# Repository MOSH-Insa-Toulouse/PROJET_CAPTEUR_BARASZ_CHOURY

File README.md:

# PROJET_CAPTEUR_BARASZ_CHOURY
 
## SOMMAIRE 
* 1 [Introduction](#introduction)
* 2 [Installation de la chaine de mesure](#paragraph2)
* 3 [Modélisation de la carte PCB sur KiCad](#paragraph3)
* 4 [Fabrication du shield et soudure des composants](#paragraph4)
* 5 [Arduino UNO](#paragraph5) 
    *  5.1 [Description du code](#subparagraph5.1) 
    *  5.2 [Bibliothèques Arduino](#subparagraph5.2)
* 6 [Application APK](#paragraph6)
* 7 [Mise en oeuvre du banc de test](#paragraph7)
    *  7.1 [Protocole](#paragraph7.1)
    *  7.2 [Résultats obtenus](#paragraph7.2)
* 8 [Améliorations à apporter](#paragraph8)

--------- 
## Introduction 
2020-2021 : Ce projet a été réalisé dans le cadre de l'unité de formation _"Du capteur au banc de test"_ de 4ième année Génie Physique à l'INSA Toulouse.
L’objectif est la conception d’un capteur de déformation (jauge de déformation) à base de graphite, peu coûteux, flexible, léger, et avant tout écoresponsable. 

Le coloriage au crayon laisse une fine couche de graphite sur le papier. Cette couche de graphite possède un réseau percolé caractéristique. Toute déformation de ce réseau induit une variation de la distance entre les nanoparticules de graphite. Cette dernière est à l’origine de la modification de la conductivité électrique/résistance de la couche de graphite. 

Souhaitant acquérir et exploiter le signal associé à la résistance du capteur, nous avons réalisé un shield PCB, à l’aide du logiciel KiCad contenant un amplificateur transimpédance, des interfaces pour un module bluetooth, un écran OLED, et un encordeur rotatoir. Ce shiled PCB est ensuite inséré sur un microcontrôleur Arduino Uno, programmé à l’aide du logiciel Arduino IDE en C++. Les mesures de résistances sont également transmises par Bluetooth et répertoriées sur notre application android APK créée sur MIT App Inventor. 

La chaîne de mesure fin prête, nous avons mis au point un banc de test permettant l'étude de la variation relative de la résistance de différents type de capteurs lors de déformation en compression et tension. 

--------------------

## Installation de la chaine de mesure 

    - Imprimer le PCB, préalablement designé sur KiCad, grâce à l'empreinte Gerber. 
  
    - Vérifier l'état des pistes. 
  
    - Souder les composants et brancher l'OLED, l'encodeur rotatoir et le module Bluetooth. 
  
    - Connecter le PCB sur la carte Arduino Uno.
  
    - Connecter le microcontrolleur Arduino Uno au PC grâce au cable USB. 
  
    - Ouvrir le programme Arduino (voir dossier Arduino).   
      Sélectionner au préalable le bon port de communication Arduino puis compiler et téléverser le programme. 
  
Les valeurs de résistance/tension sont directement affichées sur l'écran OLED. Grâce à l'encodeur rotatoir, vous pouvez décider d'afficher la grandeur souhaitée. Ces dernières sont aussi disponibles sur le moniteur Arduino.
Vous pouvez aussi télécharger notre application APK pour obtenir directement les valeurs sur votre smartphone grâce à votre connexion Bluetooth. 

-------------------

## Modélisation de la carte PCB sur KiCad 

Réalisation de la carte PCB sur KiCad  
   
    - Creation des symboles de l'OLED, le module bluetooth, l'encodeur rotatoir et le capteur graphite.
      Tous les symboles sont répertoriés dans le dossier KiCad. 

    - Schéma electrique du circuit sur eeschema. Sur ce shéma, vous trouverez un amplificateur transimpédance,
      l'écran OLED, le module Bluetooth et l'encodeur rotatoire. En haut à droite les pins de la carte Arduino
      sont représentées.  

    - Routage des pistes sur pcbnew.

Visualisation 2D du shield 

Visualisation 3D du shield

-------------------

## Fabrication du shield et soudure des composants 

Avec l'aide de Mme Cathy Crouzet, nous avons fabriqué la carte PCB modélisée au préalable sur le logiciel KiCad. Notre carte PCB est constituée d'une plaque isolante d'epoxy recouverte d'une très fine feuille de cuivre. Une couche de résine photosensible est déposée sur ce support epoxy cuivré.

Tout d'abord, le tracé de notre modélisation PCB est imprimé sur un support transparant aux ultraviolets de type papier calque : on obtient le masque (ou typon). Celui ci est placé sur la plaquette epoxy, dans l'insoleuse à tube UV, en prenant soin de poser le côté encré au contact du cuivre. Lors de l'insolation de la plaque (réalisée en 1'30"- 2'30"), les parties du typon correspondant aux pistes du circuit empêchent les UV d'atteindre la surface sensible.   
La plaque est ensuite plongée quelques secondes dans un liquide appelé révélateur. Celui ci dissout la résine exposée aux UV lors de l'insolation. A la fin de cette étape, la résine est seulement conservée dans les zones destinées aux pistes de notre circuit.

Après une étape de rinçage à l'eau courante, la plaquette doit par la suite être gravée. Pour cela, nous la plongeons dans un bain de perchlorure de fer pendant 10 minutes environ. Les parties de cuivre non protégées par la résine photosensible sont ici dissoues. Enfin, la dernière étape du processus consiste à retirer l'excès de résine en utilisant de l'acétone. 

La carte PCB ainsi obtenue est fin prête pour les étapes de perçage et de mise en place des composants. 

  * Perçage des trous de la plaque obtenugrâce à une perçeuse électrique 
Nous perçons des trous de diamètre égale à :
      * 0.8mm pour l'AOP, les résistances et les capacités.
      * 1mm pour les connecteurs de l'Arduino, le module Bluetooth, l'écran OLED, l'encodeur rotatoire et les pinces du capteur.
 
  * Soudure des composants
 
Les composants sont soudés sur la carte PCB à l'aide d'un fer à souder. 
 
----------------------

## Arduino UNO 

### Description du code 

Le code Arduino permet de lire les valeurs de tension du capteur de graphite et calcule la valeur de résistance correspondante. Il assure l'affichage des valeurs de tension et de résistance sur un écran OLED. De plus, le code permet la gestion d'un menu via l'encodeur rotatoire: l'utilisateur peut décider d'afficher la valeur de la résistance ou bien celle de la tension. 

Le code permet aussi de communiquer par Bluetooth avec le télephone portable grâce. Il envoie la mesure de la tension du capteur de graphite par Bluetooth. 

### Bibliothèques Arduino 

Afin d'utiliser le code Arduino, il vous faudra au préalable télécharger des bibliothèques Arduino.

À installer depuis l'IDE ou GitHub :

- Adafruit GFX Library : https://github.com/adafruit/Adafruit-GFX-Library
- Adafruit SSD1306 : https://github.com/adafruit/Adafruit_SSD1306
- Adafruit BusIO : https://github.com/adafruit/Adafruit_BusIO  

Vous pouvez aussi télécharger ces bibliothèques direcetement sur l'application Arduino

1) Dans l’IDE Arduino cliquez sur "croquis", allez sur "inclure un bibliothèque" puis cliquez sur  "Gerer les bibliothèques".  

2) Une fenêtre apparait. Tappez le nom de la bibliothèques que vous voulez ajouter dans la barre de recherche et cliquez sur  "Installer".Fermez la fenêtre.  

3) Dans l’IDE Arduino cliquez sur "croquis", allez sur "inclure un bibliothèque". A la fin dans les "bibliothèques contribuées" doit se trouver votre biblothèques téléchargée.  

4) Afin de savoir comment fonctionne la bibliothèque installée, vous pourrez vous servir de la page d’aide qui accompagne généralement la bibliothèque ou alors vous aider des exemples fournis avec celle-ci disponible ici :  

------------------------------

## Application APK 

L'application APK est une applictaion pour smartphone utilisant le système d'exploitation Android. 
Vous pouvez télecharger l'application grâce au fichier .apk qui vous est fourni dans notre dossier APK Bluetooth.  
Si vous souhaitez modifier l'application, vous pouvez utiliser le fichier .aia sur l'application en ligne _MIT APP INVENTOR_.  

Notre application est à mettre en relation avec le code Arduino développé pour mesurer la tension de la couche de graphite. L'application permet de :
  * se connecter à un module Bluetooth.
  * une fois connecté, relever la  valeur de la tension de la couche de graphite envoyée par Bluetooth.
  * calculer la résistance correspondante.
  * afficher ces deux valeurs de tension et de résistance
  * tracer un graphe décrivant l'évolution de la tension au cours du temps.  

----------------------------

## Mise en oeuvre du banc de test  

### Protocole 

Le protocole du banc de test est détaillé dans le fichier "Protocole du banc de test". Veuillez trouver ci joint le lien de ce fichier :https://github.com/MOSH-Insa-Toulouse/PROJET_CAPTEUR_BARASZ_CHOURY/blob/c4a42f93ef4b2496bb2e2b371ca4b9b335598a01/Banc%20de%20test/Protocole%20de%20notre%20banc%20de%20test.pdf

### Résultats obtenus 

Résultats obtenus sont détaillés au lien suivant : https://github.com/MOSH-Insa-Toulouse/PROJET_CAPTEUR_BARASZ_CHOURY/blob/7fd93865a4fc5e2c620f3dd2ebc7bdd68492d652/Banc%20de%20test/R%C3%A9sultats%20Banc%20de%20Test.xlsx 

Les analyses de nos résultats : https://github.com/MOSH-Insa-Toulouse/PROJET_CAPTEUR_BARASZ_CHOURY/blob/7fd93865a4fc5e2c620f3dd2ebc7bdd68492d652/Banc%20de%20test/Analyse%20de%20nos%20r%C3%A9sultats%20banc%20de%20test.pdf 

----------------------------

## Améliorations à apporter  
 
Notre banc de test présente certaines limites. On peut critiquer notamment : 
   - le dépôt de graphite sur le papier : on ne peut maitriser la quantité de graphite déposée sur le papier, la précision du coloriage.
   - la non répétabilité de la mesure. En effet, entre chaque série de mesures, les déformations appliquées peuvent varier: le banc de test ne permet pas d’appliquer une       déformation identique. On pourrait envisager un banc de test fonctionnant avec un servomoteur par exemple. Ce système permet de générer des contraintes avec des consignes d’angles bien présice et d'obtenir, de ce fait, une meilleure reproductibilité. 
   - la déformation irréversible du capteur entre chaque série de mesures. 

Notre carte shield peut être également améliorée. En effet, afin de pouvoir lire une plus grande plage de résistance tout en ayant des mesures stables, il faudrait pouvoir changer le gain du circuit transimpédance c'est à dire modifier la résistance R2 (voir schéma KiCad ). Cependant nous l'avons soudée sur le circuit PCB. Il aurait donc fallu : 
    
   - ne pas souder cette résistance pour pouvoir mettre des résistances différentes
   - souder une résistance variable (potentiomètre).   

Un code Arduino plus complet pourrait également être développé. Si nous travaillons avec une résistance R2 variable, le code doit prendre en compte la modification de la valeur de R2. Le code Arduino pourrait gérer un encodeur rotatoire permttant de modifier la valeur de R2 dans le code.

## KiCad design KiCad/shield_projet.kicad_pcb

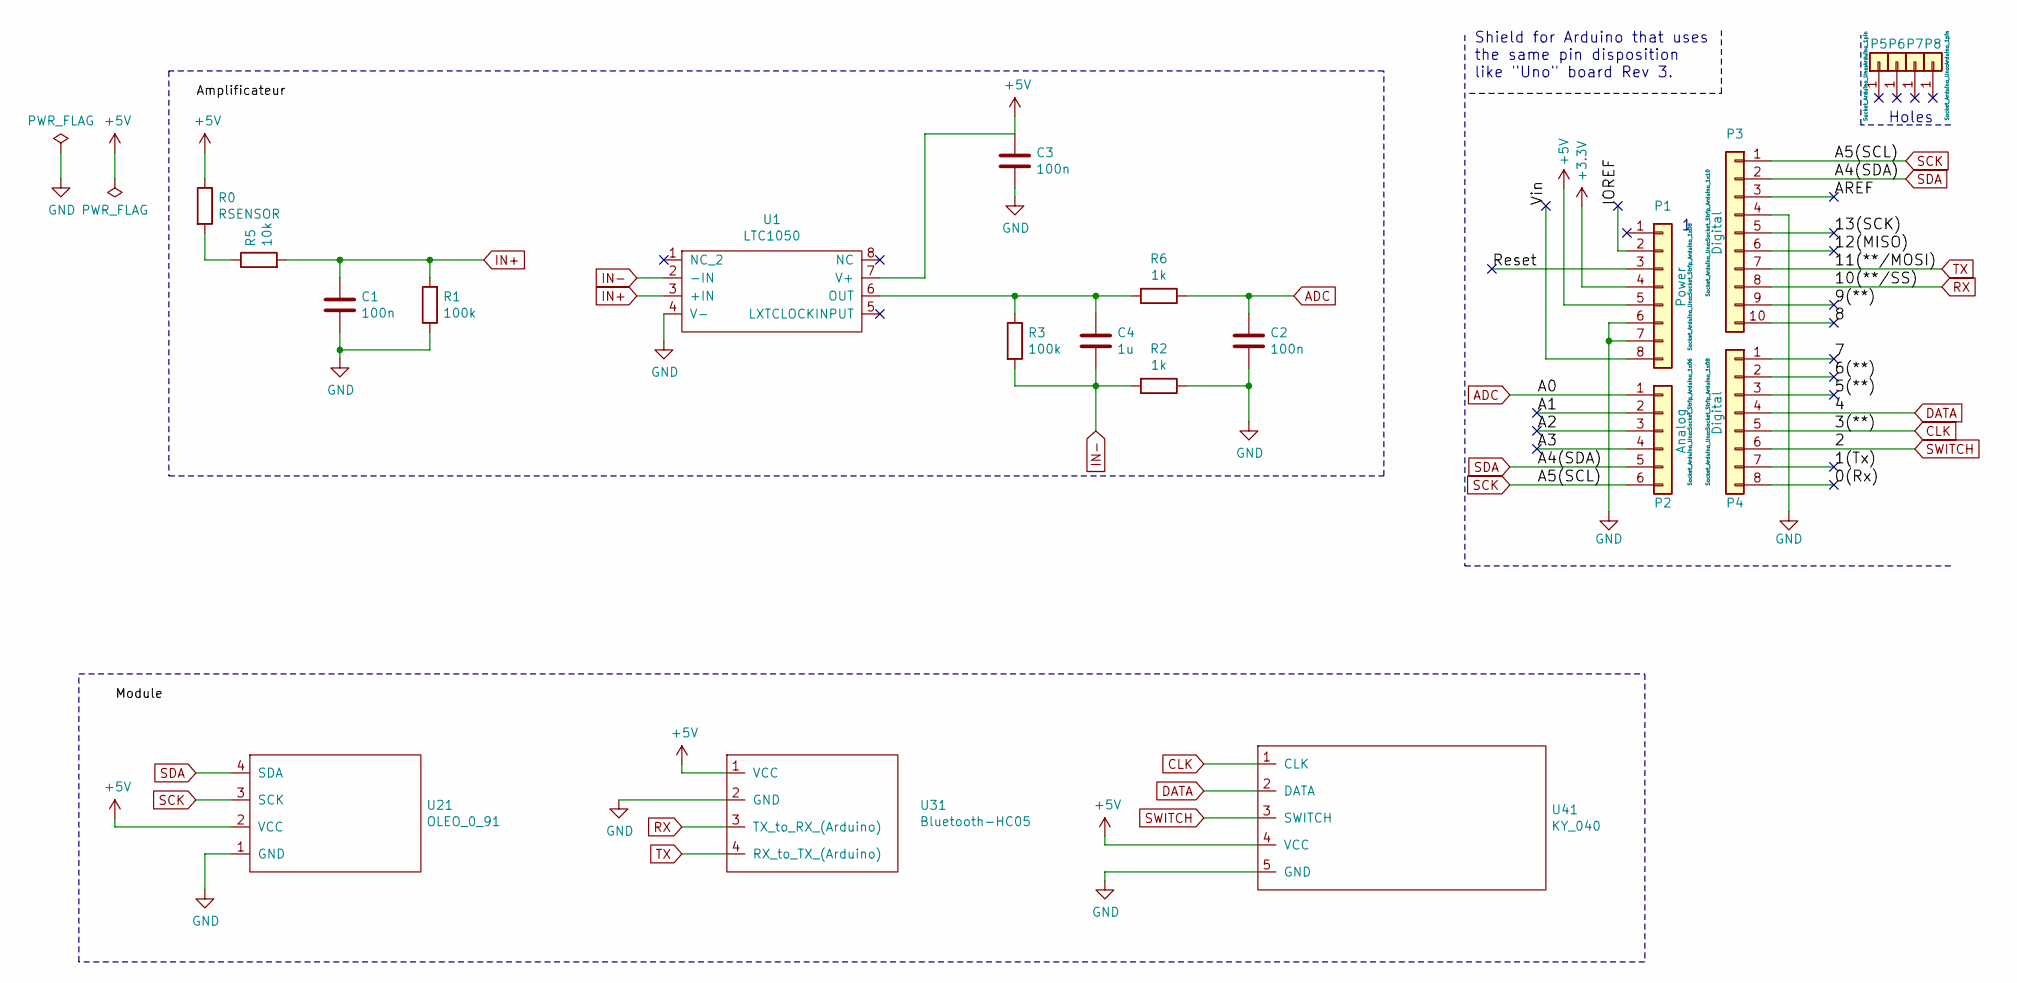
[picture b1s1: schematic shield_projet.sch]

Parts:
C1, C2, C3: 100n; C_Axial_L5.1mm_D3.1mm_P7.50mm_Horizontal
C4: 1u; C_Axial_L5.1mm_D3.1mm_P7.50mm_Horizontal
P1: Power; Socket_Strip_Arduino_1x08
P2: Analog; Socket_Strip_Arduino_1x06
P3: Digital; Socket_Strip_Arduino_1x10
P4: Digital; Socket_Strip_Arduino_1x08
P5, P6, P7, P8: CONN_01X01; Arduino_1pin
R0: RSENSOR; R_Axial_DIN0207_L6.3mm_D2.5mm_P10.16mm_Horizontal
R1, R3: 100k; R_Axial_DIN0207_L6.3mm_D2.5mm_P10.16mm_Horizontal
R2, R6: 1k; R_Axial_DIN0207_L6.3mm_D2.5mm_P10.16mm_Horizontal
R5: 10k; R_Axial_DIN0207_L6.3mm_D2.5mm_P10.16mm_Horizontal
U1: LTC1050; DIP-8_296
U21: OLEO_0_91; SIP-4
U31: Bluetooth-HC05; SIP-4_bt
U41: KY_040; SIP-5

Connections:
+3V3: P1.4
+5V: C3.1, P1.5, R0.1, U1.7 (V+), U21.2 (VCC), U31.1 (VCC), U41.4 (VCC)
/0(Rx): P4.8
/1(Tx): P4.7
/5(**): P4.3
/6(**): P4.2
/7: P4.1
/8: P3.10
/9(**): P3.9
/12(MISO): P3.6
/13(SCK): P3.5
/A1: P2.2
/A2: P2.3
/A3: P2.4
/AREF: P3.3
/IOREF: P1.2
/Reset: P1.3
/Vin: P1.8
ADC: C2.1, P2.1, R6.1
CLK: P4.5, U41.1 (CLK)
DATA: P4.4, U41.2 (DATA)
GND: C1.2, C2.2, C3.2, P1.6, P1.7, P3.4, R1.1, R2.1, U1.4 (V-), U21.1 (GND), U31.2 (GND), U41.5 (GND)
IN+: C1.1, R1.2, R5.2, U1.3 (+IN)
IN-: C4.2, R2.2, R3.2, U1.2 (-IN)
unnamed: C4.1, R3.1, R6.2, U1.6 (OUT)
unnamed: R0.2, R5.1
RX: P3.8, U31.3 (TX_to_RX_(Arduino))
SCK: P2.6, P3.1, U21.3 (SCK)
SDA: P2.5, P3.2, U21.4 (SDA)
SWITCH: P4.6, U41.3 (SWITCH)
TX: P3.7, U31.4 (RX_to_TX_(Arduino))

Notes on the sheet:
Holes
Shield for Arduino that uses the same pin disposition like "Uno" board Rev 3.

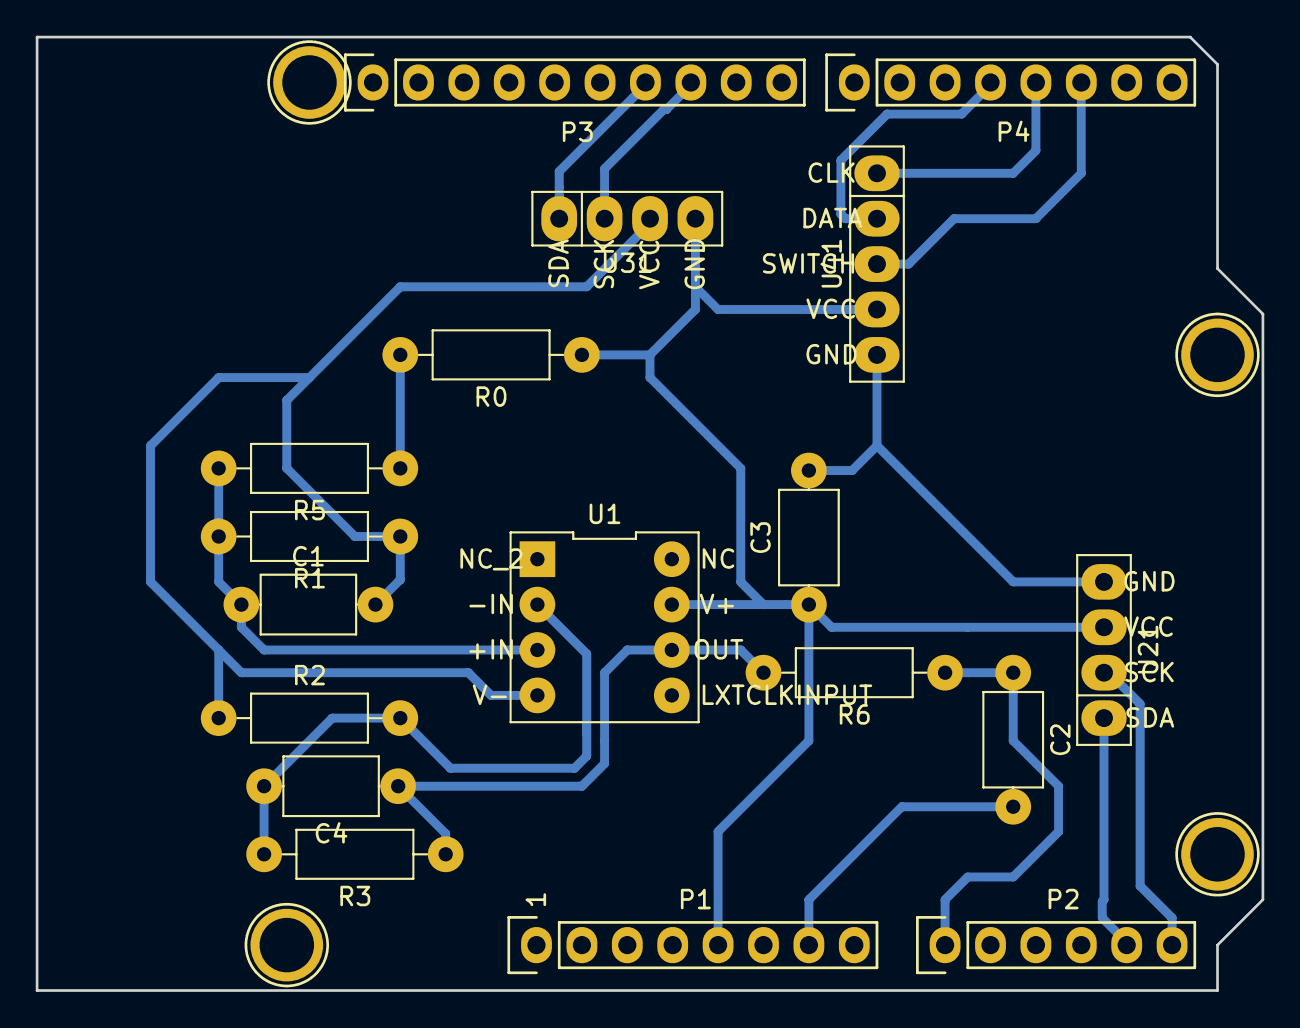
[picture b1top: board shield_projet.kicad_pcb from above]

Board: 2 copper layers, 68.6 x 53.3 mm, 22 parts (0 on the bottom side), 14 nets.

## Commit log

2021-04-20 Create LICENSE
2021-04-20 Create Adafruit_SSD1306
2021-04-20 gh repo clone adafruit/Adafruit_SSD1306
2021-04-20 Create code Arduino
2021-04-20 Create A
2021-04-20 Create b
2021-04-21 Rename DIP-8_296.kicad_mod to LTC1050.kicad_mod
2021-04-21 Create LTC1050
2021-04-21 Rename KiCad/module bluetooth/a to KiCad/Module bluetooth/a
2021-04-27 Create hey
2021-04-28 banc de test
2021-05-17 Add files via upload
    results analysis
